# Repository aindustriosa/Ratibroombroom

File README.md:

# Ratibroombroom

This repository contains de design files for the electronics part of Ratibroombroom, a maze solving robot designed at [A industriosa](https://aindustriosa.org/).

The board includes an STM32F405RGT6 microcontroller and two DRV8835 H-bridge drivers moving two 610 coreless motors for locomotion. The robot will also include a suction fan mounted on top with another 610 coreless motor driven directly with an IRLML6344 mosfet.

In the sensing aspect, the robot includes four SFH4045N IR LEDs paired with four PT12-21B/TR8 IR photodiodes for wall detection and positioning inside the maze. AS5145B magnetic encoders are used to measure motor movement precisely. The robot includes an MPU9250 9 axis IMU.

For HMI, we included two tactile switches, four LEDs and a buzzer. We are also working in an external OLED display that could be mounted in a separate module.

>THIS IS A WORK IN PROGRESS AND WILL BE UPDATED AS WE ADVANCE IN THE DEVELOPMENT

## Software

The software for this robot will be available in the following repository: [https://github.com/aindustriosa/RatibroombroomSW/](https://github.com/aindustriosa/RatibroombroomSW/)

## Pinout 

Pin # | Function | Peripheral |
----|----|----|
2 | PC13 | Right button (SW2) | 
8 | PC0 | Receiver front right (Q6)  | 
9 | PC1 | Receiver side right (Q8) | 
10 | PC2 | Receiver side left (Q7) | 
11 | PC3 | Receiver front left (Q5) | 
14 | PA0 | LED front left (D7) | 
15 | PA1 | LED front right (D8) | 
16 | PA2 | LED back left (D9)  | 
17 | PA3 | LED back right (D10) | 
20 | PA4 | Emitter front right (D3) | 
21 | PA5 | Emitter side right (D5) | 
22 | PA6 | Emitter side left (D4) | 
23 | PA7 | Emitter front left (D2) | 
24 | PC4 | Battery voltage measurement | 
29 | PB10 | I2C SCL (J3) | 
30 | PB11 | I2C SDA (J3) | 
33 | PB12 | Left button (SW1) |  
35 | PB14 | IMU FSYNC (U4) | 
36 | PB15 | IMU INT (U4) | 
37 | PC6 | Right motor direction (U7) | 
38 | PC7 | Right motor PWM (U7) | 
39 | PC8 | Left motor direction (U2) | 
40 | PC9 | Left motor PWM (U2) | 
42 | PA9 | Serial RX (J3) | 
43 | PA10 | Serial TX (J3) | 
46 | PA13 | SWDIO (J3) | 
49 | PA14 | SWCLK (J3) | 
50 | PA15 | IMU CS (U4) | 
51 | PC10 | IMU SCK (U4) | 
52 | PC11 | IMU MISO (U4) | 
53 | PC12 | IMU MOSI (U4) | 
56 | PB4 | Encoder left, channel A | 
57 | PB5 | Encoder left, channel B | 
58 | PB6 | Encoder right, channel B | 
59 | PB7 | Encoder right, channel A | 
61 | PB8 | Suction fan PWM | 
62 | PB9 | Buzzer (BZ1) | 

## References

This project is heavily based on the work of [cua-cua](https://github.com/cua-cua) and [peque](https://github.com/peque) from [Bulebots](https://github.com/Bulebots) in their projects [Bulebule](https://github.com/Bulebots/bulebule) and [Meiga](https://github.com/Bulebots/meiga)

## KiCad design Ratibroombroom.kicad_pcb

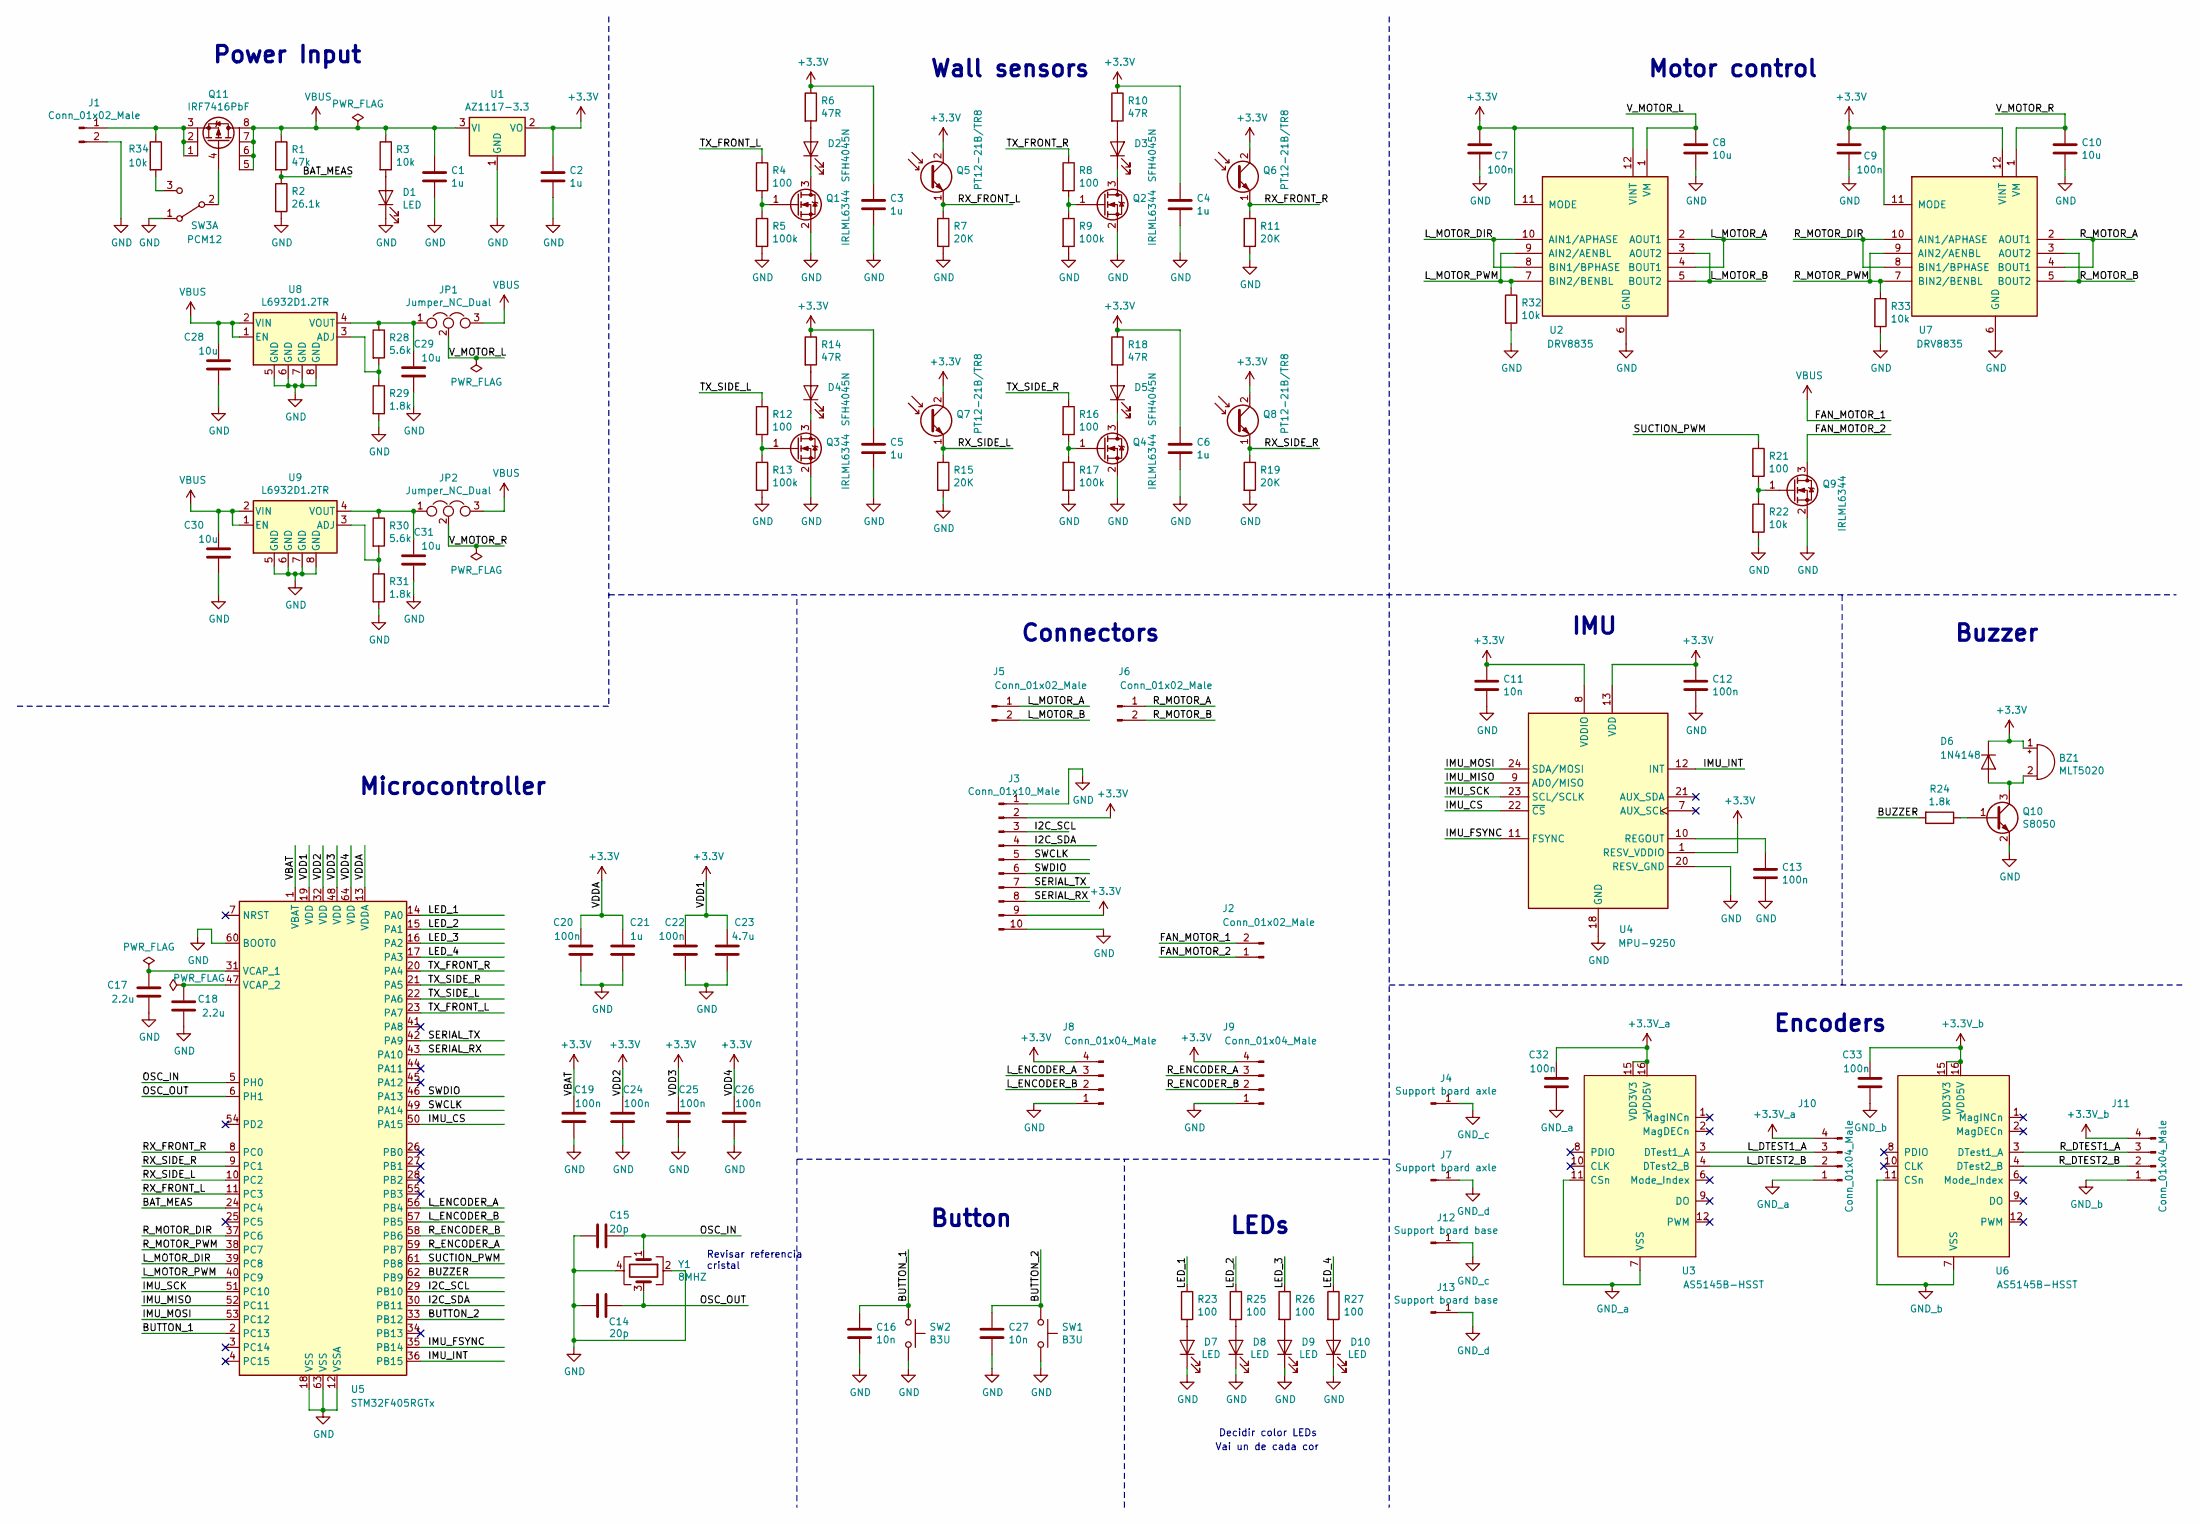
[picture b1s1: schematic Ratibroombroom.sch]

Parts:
BZ1: MLT5020; MLT-5020
C1, C2, C3, C4, C5, C6, C21: 1u; C_0603_1608Metric
C7, C9, C12, C13, C19, C20, C22, C24, C25, C26, C32, C33: 100n; C_0603_1608Metric
C8, C10, C28, C29, C30, C31: 10u; C_0603_1608Metric
C11, C16, C27: 10n; C_0603_1608Metric
C14, C15: 20p; C_0603_1608Metric
C17, C18: 2.2u; C_0603_1608Metric
C23: 4.7u; C_0603_1608Metric
D1, D7, D8, D9, D10: LED; LED_0603_1608Metric
D2, D3, D4, D5: SFH4045N
D6: 1N4148; D_SOD-323
J1: Conn_01x02_Male; JST_XH_B2B-XH-A_1x02_P2.50mm_Vertical
J2, J5, J6: Conn_01x02_Male; Pad_SMD_2P_1x3mm
J3: Conn_01x10_Male; PinHeader_2x05_P1.27mm_Vertical
J4, J7: Support board axle; Encoder_axle_hole
J8, J9: Conn_01x04_Male; Pad_SMD_4P_1x3mm
J10, J11: Conn_01x04_Male; Pad_SMD_4P_1x1.5mm
J12, J13: Support board base; Encoder_base_connector
JP1, JP2: Jumper_NC_Dual; SolderJumper-3_P1.3mm_Open_RoundedPad1.0x1.5mm_NumberLabels
Q1, Q2, Q3, Q4, Q9: IRLML6344; SOT-23
Q5, Q6, Q7, Q8: PT12-21B/TR8; PT12-21B-TR8
Q10: S8050; SOT-23
Q11: IRF7416PbF; SO-8_5.3x6.2mm_P1.27mm
R1: 47k; R_0603_1608Metric
R2: 26.1k; R_0603_1608Metric
R3, R22, R32, R33, R34: 10k; R_0603_1608Metric
R4, R8, R12, R16, R21, R23, R25, R26, R27: 100; R_0603_1608Metric
R5, R9, R13, R17: 100k; R_0603_1608Metric
R6, R10, R14, R18: 47R; R_0603_1608Metric
R7, R11, R15, R19: 20K; R_0603_1608Metric
R24, R29, R31: 1.8k; R_0603_1608Metric
R28, R30: 5.6k; R_0603_1608Metric
SW1, SW2: B3U; SW_SPST_B3U-1000P
SW3: PCM12; SW_SPDT_PCM12
U1: AZ1117-3.3; SOT-223-3_TabPin2
U2, U7: DRV8835; WSON-12-1EP_3x2mm_P0.5mm_EP1x2.65_ThermalVias
U3, U6: AS5145B-HSST; SSOP-16_5.3x6.2mm_P0.65mm
U4: MPU-9250; QFN-24-1EP_3x3mm_P0.4mm_EP1.75x1.6mm
U5: STM32F405RGTx; LQFP-64_10x10mm_P0.5mm
U8, U9: L6932D1.2TR; SO-8_5.3x6.2mm_P1.27mm
Y1: 8MHZ; Crystal_SMD_5032-4Pin_5.0x3.2mm

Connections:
+3.3V_a: C32.2, J10.4, U3.15 (VDD3V3), U3.16 (VDD5V)
+3.3V_b: C33.2, J11.4, U6.15 (VDD3V3), U6.16 (VDD5V)
+3V3: BZ1.1 (-), C2.1, C3.1, C4.1, C5.1, C6.1, C7.1, C9.1, C11.1, C12.1, C19.2, C20.2, C21.2, C22.2, C23.2, C24.2, C25.2, C26.2, D6.1 (K), J3.2, J3.9, J8.4, J9.4, Q5.2 (C), Q6.2 (C), Q7.2 (C), Q8.2 (C), R6.1, R10.1, R14.1, R18.1, U1.2 (VO), U2.11 (MODE), U2.12 (VINT), U4.1 (RESV_VDDIO), U4.8 (VDDIO), U4.13 (VDD), U5.1 (VBAT), U5.13 (VDDA), U5.19 (VDD), U5.32 (VDD), U5.48 (VDD), U5.64 (VDD), U7.11 (MODE), U7.12 (VINT)
/BAT_MEAS: R1.2, R2.1, U5.24 (PC4)
/BUTTON_1: C16.1, SW2.1, U5.2 (PC13)
/BUTTON_2: C27.1, SW1.1, U5.33 (PB12)
/BUZZER: R24.2, U5.62 (PB9)
/FAN_MOTOR_2: J2.1, Q9.3 (D)
/I2C_SCL: J3.3, U5.29 (PB10)
/I2C_SDA: J3.4, U5.30 (PB11)
/IMU_CS: U4.22 (~CS), U5.50 (PA15)
/IMU_FSYNC: U4.11 (FSYNC), U5.35 (PB14)
/IMU_INT: U4.12 (INT), U5.36 (PB15)
/IMU_MISO: U4.9 (AD0/MISO), U5.52 (PC11)
/IMU_MOSI: U4.24 (SDA/MOSI), U5.53 (PC12)
/IMU_SCK: U4.23 (SCL/SCLK), U5.51 (PC10)
/LED_1: R23.1, U5.14 (PA0)
/LED_2: R25.1, U5.15 (PA1)
/LED_3: R26.1, U5.16 (PA2)
/LED_4: R27.1, U5.17 (PA3)
/L_DTEST1_A: J10.3, U3.3 (DTest1_A)
/L_DTEST2_B: J10.2, U3.4 (DTest2_B)
/L_ENCODER_A: J8.3, U5.56 (PB4)
/L_ENCODER_B: J8.2, U5.57 (PB5)
/L_MOTOR_A: J5.1, U2.2 (AOUT1), U2.4 (BOUT1)
/L_MOTOR_B: J5.2, U2.3 (AOUT2), U2.5 (BOUT2)
/L_MOTOR_DIR: U2.8 (BIN1/BPHASE), U2.10 (AIN1/APHASE), U5.39 (PC8)
/L_MOTOR_PWM: R32.1, U2.7 (BIN2/BENBL), U2.9 (AIN2/AENBL), U5.40 (PC9)
/OSC_IN: C15.1, U5.5 (PH0), Y1.1
/OSC_OUT: C14.1, U5.6 (PH1), Y1.3
/RX_FRONT_L: Q5.1 (E), R7.1, U5.11 (PC3)
/RX_FRONT_R: Q6.1 (E), R11.1, U5.8 (PC0)
/RX_SIDE_L: Q7.1 (E), R15.1, U5.10 (PC2)
/RX_SIDE_R: Q8.1 (E), R19.1, U5.9 (PC1)
/R_DTEST1_A: J11.3, U6.3 (DTest1_A)
/R_DTEST2_B: J11.2, U6.4 (DTest2_B)
/R_ENCODER_A: J9.3, U5.59 (PB7)
/R_ENCODER_B: J9.2, U5.58 (PB6)
/R_MOTOR_A: J6.1, U7.2 (AOUT1), U7.4 (BOUT1)
/R_MOTOR_B: J6.2, U7.3 (AOUT2), U7.5 (BOUT2)
/R_MOTOR_DIR: U5.37 (PC6), U7.8 (BIN1/BPHASE), U7.10 (AIN1/APHASE)
/R_MOTOR_PWM: R33.1, U5.38 (PC7), U7.7 (BIN2/BENBL), U7.9 (AIN2/AENBL)
/SERIAL_RX: J3.8, U5.43 (PA10)
/SERIAL_TX: J3.7, U5.42 (PA9)
/SUCTION_PWM: R21.1, U5.61 (PB8)
/SWCLK: J3.5, U5.49 (PA14)
/SWDIO: J3.6, U5.46 (PA13)
/TX_FRONT_L: R4.1, U5.23 (PA7)
/TX_FRONT_R: R8.1, U5.20 (PA4)
/TX_SIDE_L: R12.1, U5.22 (PA6)
/TX_SIDE_R: R16.1, U5.21 (PA5)
/V_MOTOR_L: C8.1, JP1.2, U2.1 (VM)
/V_MOTOR_R: C10.1, JP2.2, U7.1 (VM)
GND: C1.2, C2.2, C3.2, C4.2, C5.2, C6.2, C7.2, C8.2, C9.2, C10.2, C11.2, C12.2, C13.2, C14.2, C15.2, C16.2, C17.1, C18.1, C19.1, C20.1, C21.1, C22.1, C23.1, C24.1, C25.1, C26.1, C27.2, C28.1, C29.1, C30.1, C31.1, D1.1 (K), D7.1 (K), D8.1 (K), D9.1 (K), D10.1 (K), J1.2, J3.1, J3.10, J8.1, J9.1, Q1.2 (S), Q2.2 (S), Q3.2 (S), Q4.2 (S), Q9.2 (S), Q10.2 (E), R2.2, R5.2, R7.2, R9.2, R11.2, R13.2, R15.2, R17.2, R19.2, R22.2, R29.2, R31.2, R32.2, R33.2, SW1.2, SW2.2, SW3.1 (A), U1.1 (GND), U2.6 (GND), U4.18 (GND), U4.20 (RESV_GND), U5.12 (VSSA), U5.18 (VSS), U5.60 (BOOT0), U5.63 (VSS), U7.6 (GND), U8.5 (GND), U8.6 (GND), U8.7 (GND), U8.8 (GND), U9.5 (GND), U9.6 (GND), U9.7 (GND), U9.8 (GND), Y1.2, Y1.4
GND_a: C32.1, J10.1, U3.7 (VSS), U3.11 (CSn)
GND_b: C33.1, J11.1, U6.7 (VSS), U6.11 (CSn)
GND_c: J4.1, J12.1
GND_d: J7.1, J13.1
unnamed: BZ1.2 (+), D6.2 (A), Q10.3 (C)
unnamed: C13.1, U4.10 (REGOUT)
unnamed: C17.2, U5.31 (VCAP_1)
unnamed: C18.2, U5.47 (VCAP_2)
unnamed: C29.2, JP1.1, R28.1, U8.4 (VOUT)
unnamed: C31.2, JP2.1, R30.1, U9.4 (VOUT)
unnamed: D1.2 (A), R3.2
unnamed: D2.1 (K), Q1.3 (D)
unnamed: D2.2 (A), R6.2
unnamed: D3.1 (K), Q2.3 (D)
unnamed: D3.2 (A), R10.2
unnamed: D4.1 (K), Q3.3 (D)
unnamed: D4.2 (A), R14.2
unnamed: D5.1 (K), Q4.3 (D)
unnamed: D5.2 (A), R18.2
unnamed: D7.2 (A), R23.2
unnamed: D8.2 (A), R25.2
unnamed: D9.2 (A), R26.2
unnamed: D10.2 (A), R27.2
unnamed: J1.1, Q11.1 (S), Q11.2 (S), Q11.3 (S), R34.1
unnamed: Q1.1 (G), R4.2, R5.1
unnamed: Q2.1 (G), R8.2, R9.1
unnamed: Q3.1 (G), R12.2, R13.1
unnamed: Q4.1 (G), R16.2, R17.1
unnamed: Q9.1 (G), R21.2, R22.1
unnamed: Q10.1 (B), R24.1
unnamed: Q11.4 (G), SW3.2 (B)
unnamed: R28.2, R29.1, U8.3 (ADJ)
unnamed: R30.2, R31.1, U9.3 (ADJ)
unnamed: R34.2, SW3.3 (C)
VBUS: C1.1, C28.2, C30.2, J2.2, JP1.3, JP2.3, Q11.5 (D), Q11.6 (D), Q11.7 (D), Q11.8 (D), R1.1, R3.1, U1.3 (VI), U8.1 (EN), U8.2 (VIN), U9.1 (EN), U9.2 (VIN)

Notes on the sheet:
Power Input
Wall sensors
Motor control
Button
LEDs
IMU
Buzzer
Encoders
Microcontroller
Connectors
Decidir color LEDs
Revisar referencia cristal
Vai un de cada cor

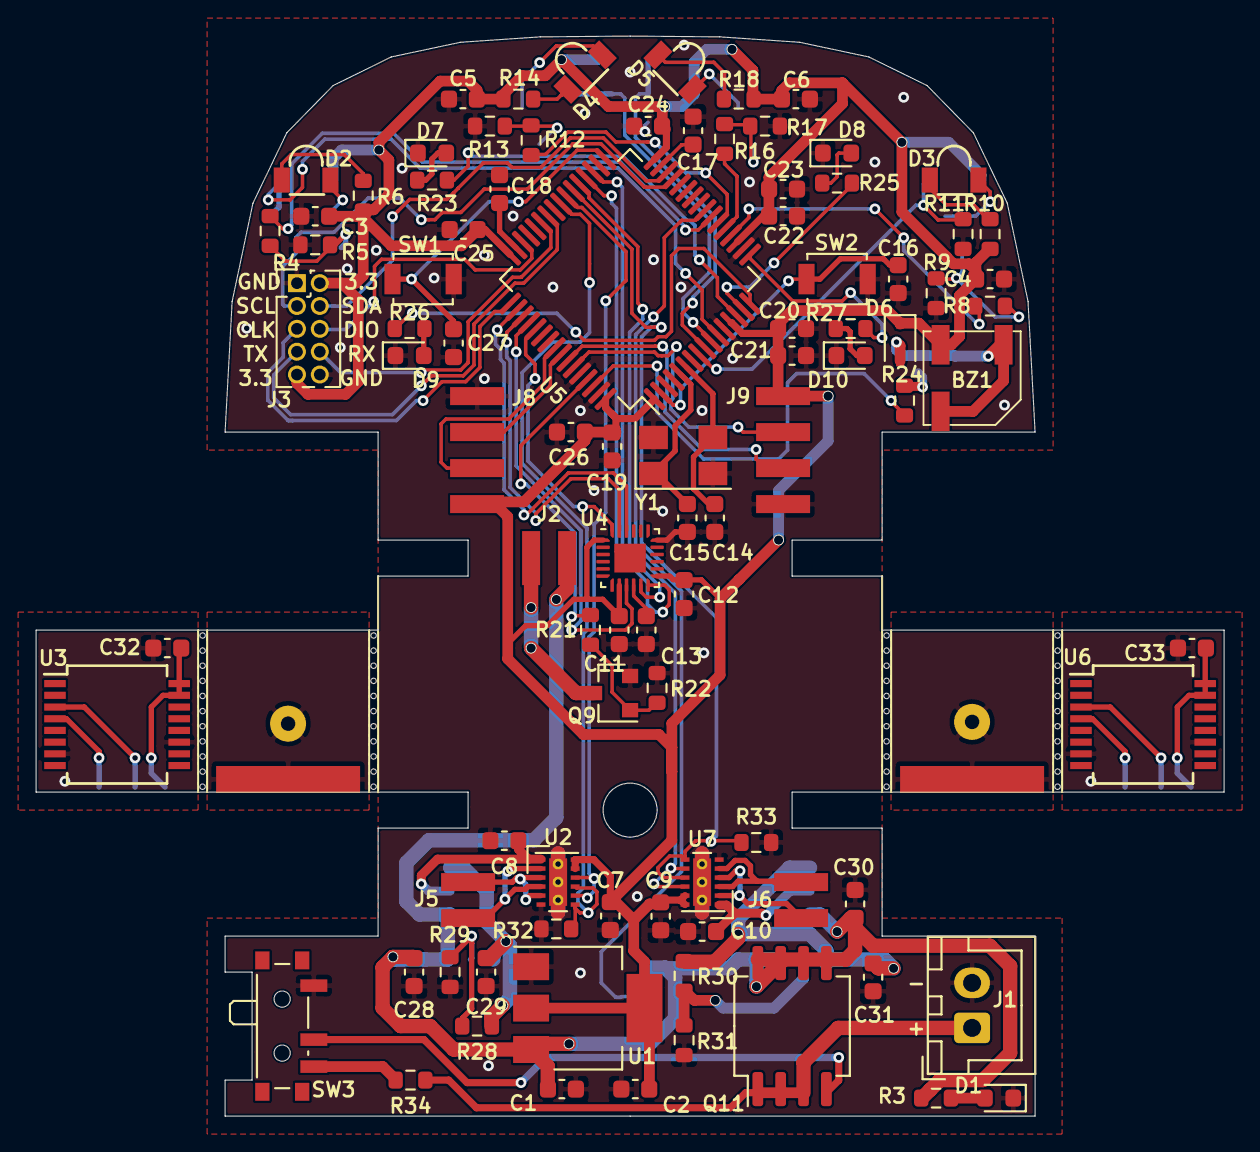
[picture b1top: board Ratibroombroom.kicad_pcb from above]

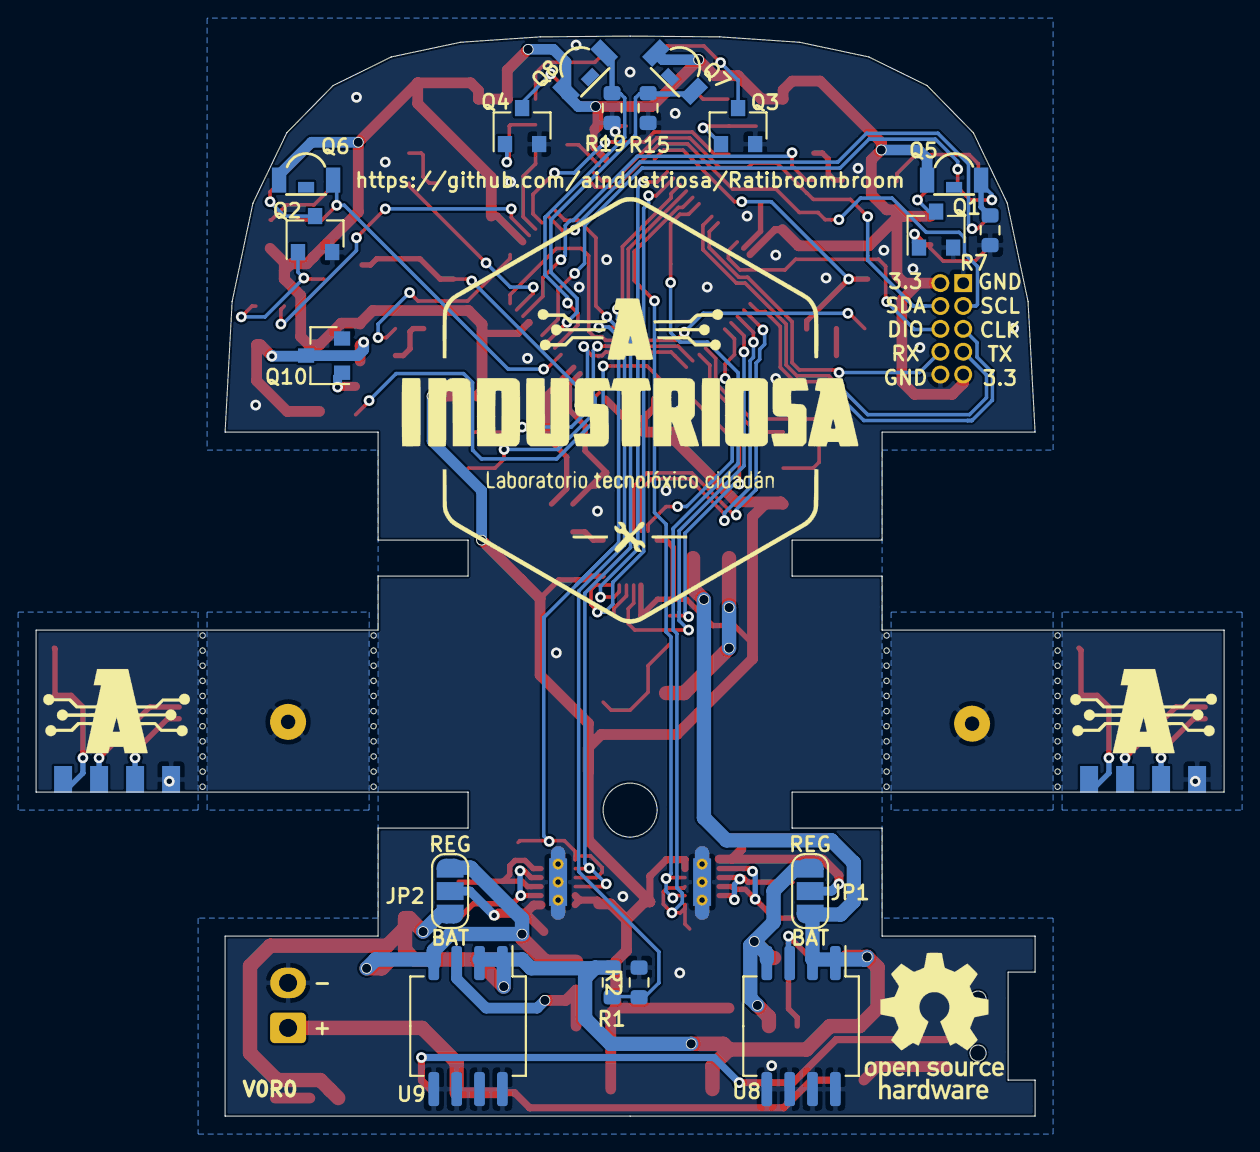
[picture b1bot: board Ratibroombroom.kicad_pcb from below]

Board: 2 copper layers, 66.0 x 60.0 mm, 116 parts (20 on the bottom side), 89 nets.

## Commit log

2020-01-16 First version of the micromouse schematic
2020-01-17 Add linear regulators to motor drivers supply. Include jumpers to select between direct (battery), regulated or none supply for the drivers.
2020-01-17 Added pull-down resistors on motor pwm lines
2020-01-17 Added comments in schematics
2020-01-17 More comments on schematics
2020-01-17 Typo fix
2020-01-18 Modify connection of capacitors in IR emitters. Add on/of switch through mosfet. Assign footprints to every schematic symbol.
2020-01-18 Added BOM parts for Power section
2020-01-19 Added BOM parts for Motor control section
2020-01-19 Added BOM parts for IMU section
2020-01-19 Added BOM parts for Buzzer section
2020-01-19 Added BOM parts for Button and LED sections
2020-01-19 Added BOM parts for Microcontroller section
2020-01-19 Added BOM parts for Encoder section
2020-01-19 Added BOM parts for Wall Sensor section
2020-01-19 Fix wrong footpring for DRV8835
2020-01-19 Add decoupling capacitors to the magnetic encoders
2020-01-19 Fix wrong footprint for MPU-9250
2020-01-19 Fix incomplete commit 51b0672
2020-01-19 Redo edge connector used for encoder boards
2020-01-19 Remove solder paste from motor and encoder board connector footprints
2020-02-14 Fix error assigning power supply to the right motor driver
2020-02-14 Add mouse 3D design file made with Freecad
2020-02-14 Add generated dxf layers for pcbnew
2020-02-14 Test dxf graphics in pcbnew
2020-02-15 Modify board to 45mm width to make everything fit. Place components in pcbnew Modify schematic to merge I2C, SWIO and UART connectors into a single 2x5 pin connector
2020-02-15 Modify 3D design to fit the 45mm width board
2020-02-15 Remove Freecad backup file
2020-02-15 Change encoder board connector footprint to single side connector
2020-09-29 Partial PCB routing
2020-10-06 More PCB routing. Add encoder magnet support boards. Include 3D models that were missing. Clean silkscreen layers. Update 3d CAD design. Include .step model of the robot.
2020-10-14 Change encoder board connectors so that the boards will be rotated in the final assembly. Add separate ground and power nets to encoder boards to pass DRC cleanly. Add some logos
2020-10-16 Add version tag in silkscreen. Change board thickness to .8 mm
2020-10-19 Add BOM references
2020-11-07 Remove discarded routing attempts
2020-11-07 Add basic info to the README file
2021-01-18 Change R24 value to 1k8 to increase buzzer loudness
2021-09-25 Include encoder axle supports in CAD design
2025-01-11 WIP: motor holder 3d design
